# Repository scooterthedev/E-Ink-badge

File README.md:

# Inky - An E-Ink badge

This is an e-ink USB-C PCB badge that I'm building since I loved the Github one so much, and want to make my own! I decided that I wanted to follow a similar design route with the Github Badge so I went with the RP2040 IC.

This was my first time designing an FPC cable from scratch on a PCB! Originally, I wanted to do it to help make a board for my brother, but in the end, I found it too complicated. For this board, I decided to use Gemini to help me, since I wasn't able to find any good documentation of how to properly wire it up.

When I first started this, I though it would take at least 10 hours from when I glanced at the Github Badge, but in the end, it only took me about 4.3 hours which was insanely quick and efficient of my time!

I have attached some photos below outlining the PCB, Schematic and even the 3D rending's on the board!

## Images

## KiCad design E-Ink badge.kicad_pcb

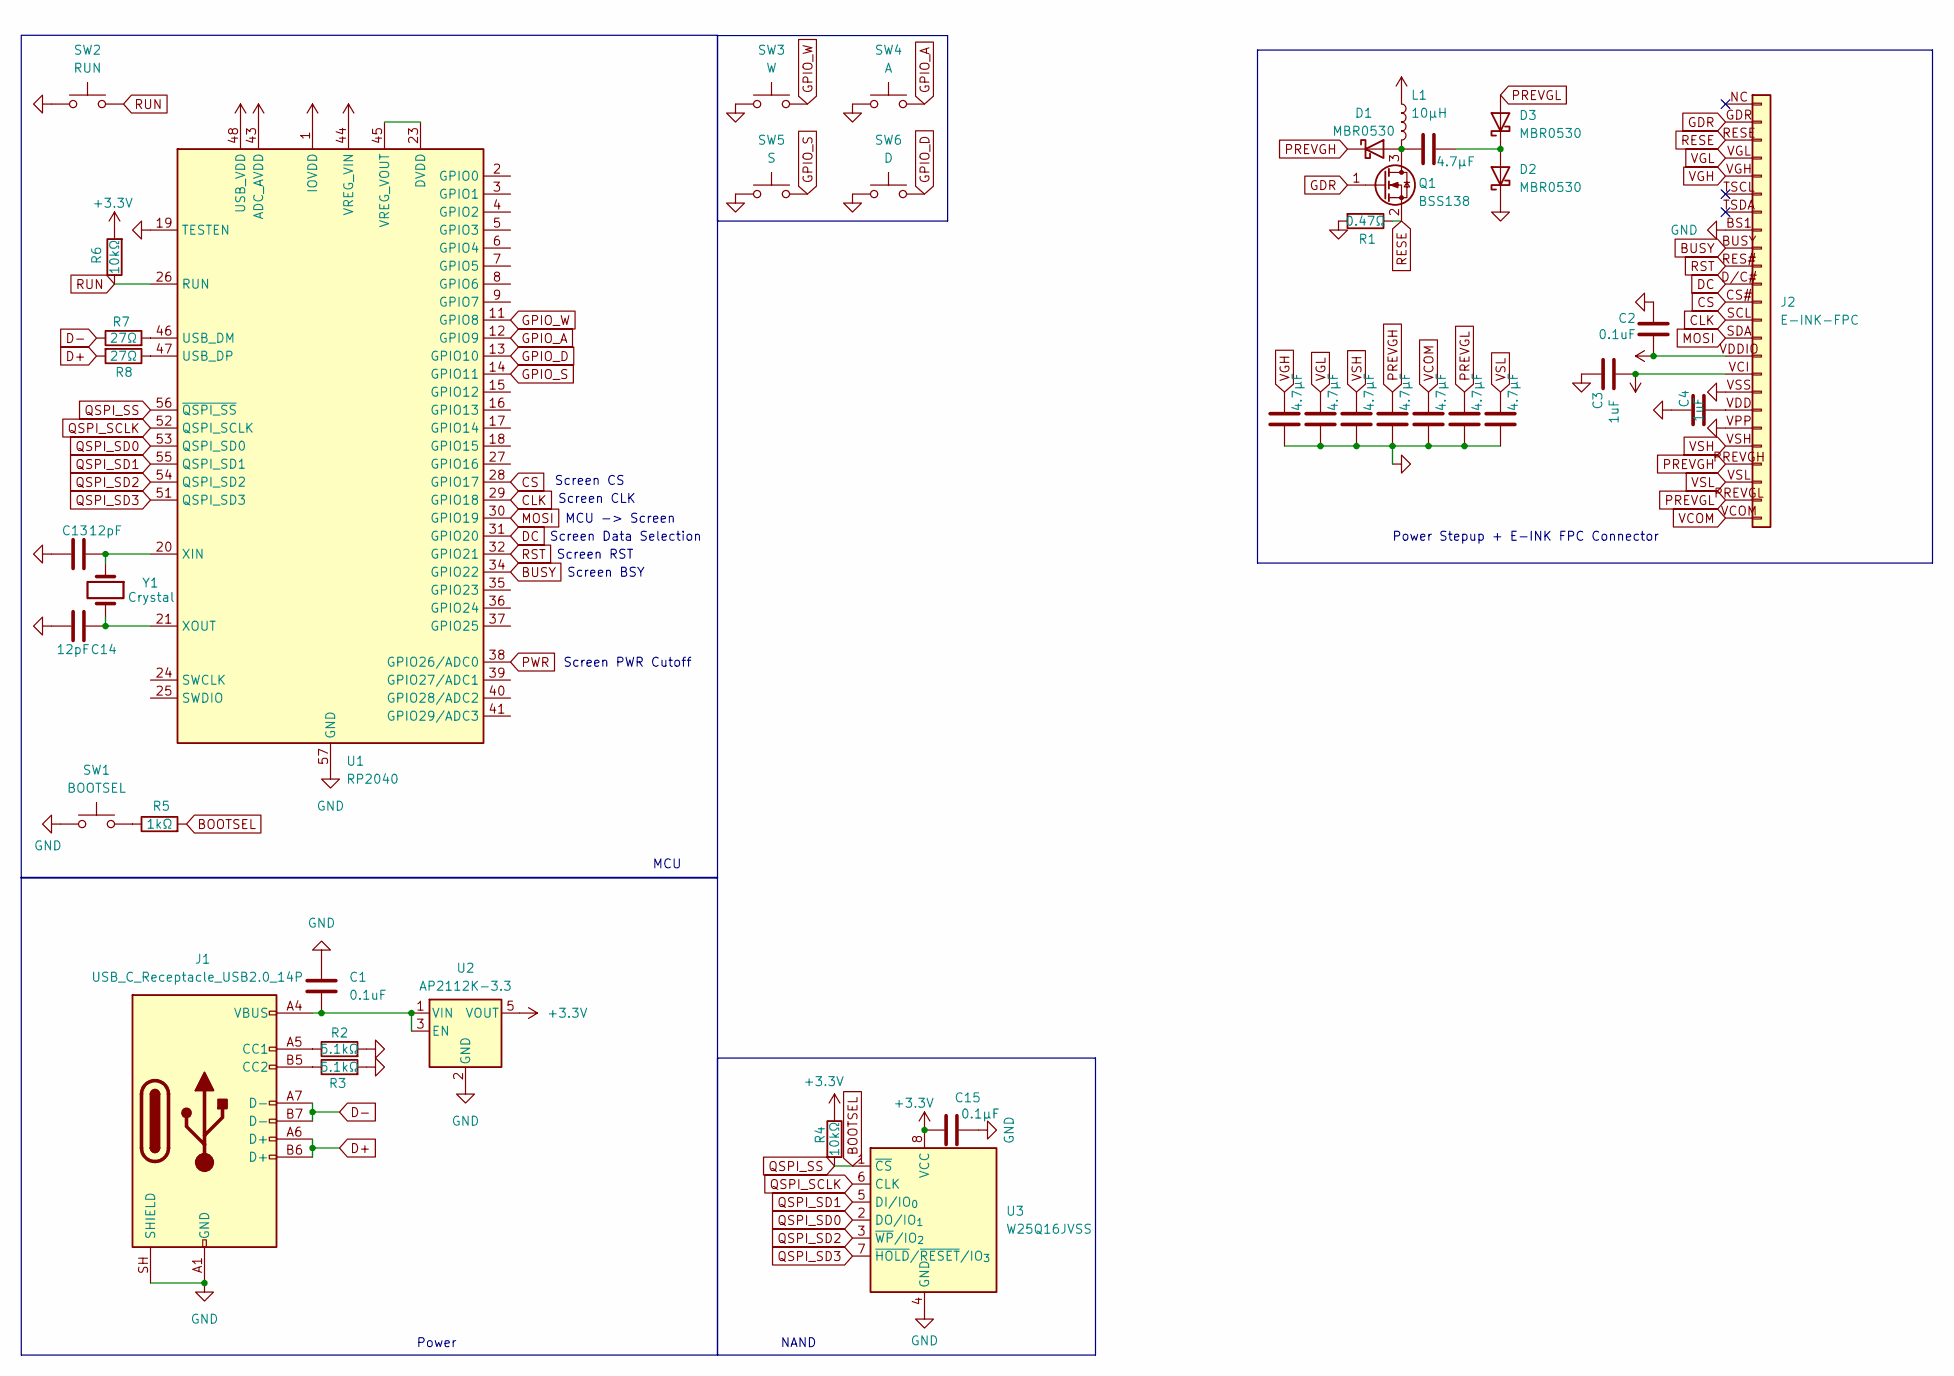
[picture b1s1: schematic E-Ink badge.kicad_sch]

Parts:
C1, C2: 0.1uF; C_0402_1005Metric
C3, C4: 1uF; C_0402_1005Metric
C5, C6, C7, C8, C9, C10, C11, C12: 4.7µF; C_0402_1005Metric
C13, C14: 12pF; C_0402_1005Metric
C15: 0.1µF; C_0402_1005Metric
D1, D2, D3: MBR0530; D_SOD-123
J1: USB_C_Receptacle_USB2.0_14P; USB_C_Receptacle_GCT_USB4105-xx-A_16P_TopMnt_Horizontal
J2: E-INK-FPC; Hirose_FH12-24S-0.5SH_1x24-1MP_P0.50mm_Horizontal
L1: 10µH; L_0805_2012Metric
Q1: BSS138; SOT-23
R1: 0.47Ω; C_0402_1005Metric
R2, R3: 5.1kΩ; C_0402_1005Metric
R4, R6: 10kΩ; C_0402_1005Metric
R5: 1kΩ; C_0402_1005Metric
R7, R8: 27Ω; C_0402_1005Metric
SW1: BOOTSEL; SW_SPST_PTS645Sx43SMTR92
SW2: RUN; SW_SPST_PTS645Sx43SMTR92
SW3: W; SW_SPST_PTS645Sx43SMTR92
SW4: A; SW_SPST_PTS645Sx43SMTR92
SW5: S; SW_SPST_PTS645Sx43SMTR92
SW6: D; SW_SPST_PTS645Sx43SMTR92
U1: RP2040; QFN-56-1EP_7x7mm_P0.4mm_EP3.2x3.2mm
U2: AP2112K-3.3; SOT-23-5
U3: W25Q16JVSS; SOIC-8_5.3x5.3mm_P1.27mm
Y1: Crystal; Crystal_SMD_3215-2Pin_3.2x1.5mm

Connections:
+3.3V: C2.1, C3.1, C15.1, J2.VCI (Pin_16), J2.VDDIO (Pin_15), L1.1, R4.1, R6.2, U1.1 (IOVDD), U1.10 (IOVDD), U1.22 (IOVDD), U1.33 (IOVDD), U1.42 (IOVDD), U1.43 (ADC_AVDD), U1.44 (VREG_VIN), U1.48 (USB_VDD), U1.49 (IOVDD), U2.5 (VOUT), U3.8 (VCC)
BOOTSEL: R4.2, R5.2, U1.56 (~QSPI_SS), U3.1 (~CS)
BUSY: J2.BUSY (Pin_9), U1.34 (GPIO22)
CLK: J2.SCL (Pin_13), U1.29 (GPIO18)
CS: J2.CS# (Pin_12), U1.28 (GPIO17)
D+: J1.A6 (D+), J1.B6 (D+), R8.2
D-: J1.A7 (D-), J1.B7 (D-), R7.1
DC: J2.D/C# (Pin_11), U1.31 (GPIO20)
GDR: J2.GDR (Pin_2), Q1.1 (G)
GND: C1.1, C2.2, C3.2, C4.2, C6.1, C7.1, C8.1, C9.1, C10.1, C11.1, C12.1, C13.2, C14.2, C15.2, D2.1 (K), J1.A1 (GND), J1.A12 (GND), J1.B1 (GND), J1.B12 (GND), J1.SH (SHIELD), J2.BS1 (Pin_8), J2.VPP (Pin_19), J2.VSS (Pin_17), R1.2, R2.2, R3.2, SW1.1, SW2.1, SW3.1, SW4.1, SW5.1, SW6.1, U1.19 (TESTEN), U1.57 (GND), U2.2 (GND), U3.4 (GND)
GPIO_A: SW4.2, U1.12 (GPIO9)
GPIO_D: SW6.2, U1.13 (GPIO10)
GPIO_S: SW5.2, U1.14 (GPIO11)
GPIO_W: SW3.2, U1.11 (GPIO8)
MOSI: J2.SDA (Pin_14), U1.30 (GPIO19)
unnamed: C5.1, D1.2 (A), L1.2, Q1.3 (D)
unnamed: C5.2, D2.2 (A), D3.1 (K)
unnamed: J1.A5 (CC1), R2.1
unnamed: J1.B5 (CC2), R3.1
unnamed: C4.1, J2.VDD (Pin_18)
unnamed: R5.1, SW1.2
unnamed: R7.2, U1.46 (USB_DM)
unnamed: R8.1, U1.47 (USB_DP)
unnamed: U1.23 (DVDD), U1.45 (VREG_VOUT), U1.50 (DVDD)
unnamed: C13.1, U1.20 (XIN), Y1.1
unnamed: C14.1, U1.21 (XOUT), Y1.2
unnamed: C1.2, J1.A4 (VBUS), J1.A9 (VBUS), J1.B4 (VBUS), J1.B9 (VBUS), U2.1 (VIN), U2.3 (EN)
PREVGH: C9.2, D1.1 (K), J2.PREVGH (Pin_21)
PREVGL: C11.2, D3.2 (A), J2.PREVGL (Pin_23)
PWR: U1.38 (GPIO26/ADC0)
QSPI_SCLK: U1.52 (QSPI_SCLK), U3.6 (CLK)
QSPI_SD0: U1.53 (QSPI_SD0), U3.2 (DO/IO_{1})
QSPI_SD1: U1.55 (QSPI_SD1), U3.5 (DI/IO_{0})
QSPI_SD2: U1.54 (QSPI_SD2), U3.3 (~WP/IO_{2})
QSPI_SD3: U1.51 (QSPI_SD3), U3.7 (~HOLD/~RESET/IO_{3})
RESE: J2.RESE (Pin_3), Q1.2 (S), R1.1
RST: J2.RES# (Pin_10), U1.32 (GPIO21)
RUN: R6.1, SW2.2, U1.26 (RUN)
VCOM: C10.2, J2.VCOM (Pin_24)
VGH: C6.2, J2.VGH (Pin_5)
VGL: C7.2, J2.VGL (Pin_4)
VSH: C8.2, J2.VSH (Pin_20)
VSL: C12.2, J2.VSL (Pin_22)

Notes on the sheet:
Screen CS
Screen BSY
Screen PWR Cutoff
Power
Power Stepup + E-INK FPC Connector
MCU
MCU -> Screen
Screen Data Selection
Screen RST
Screen CLK
NAND

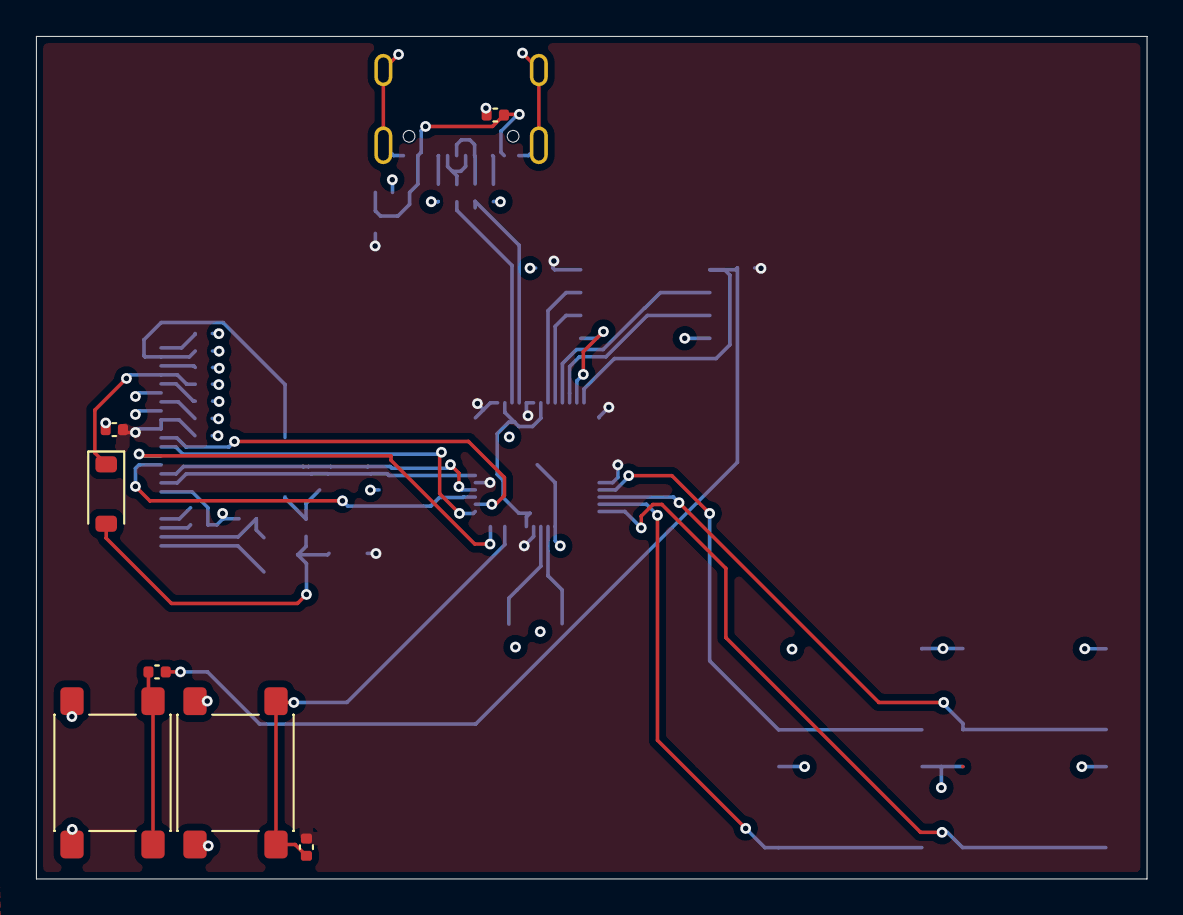
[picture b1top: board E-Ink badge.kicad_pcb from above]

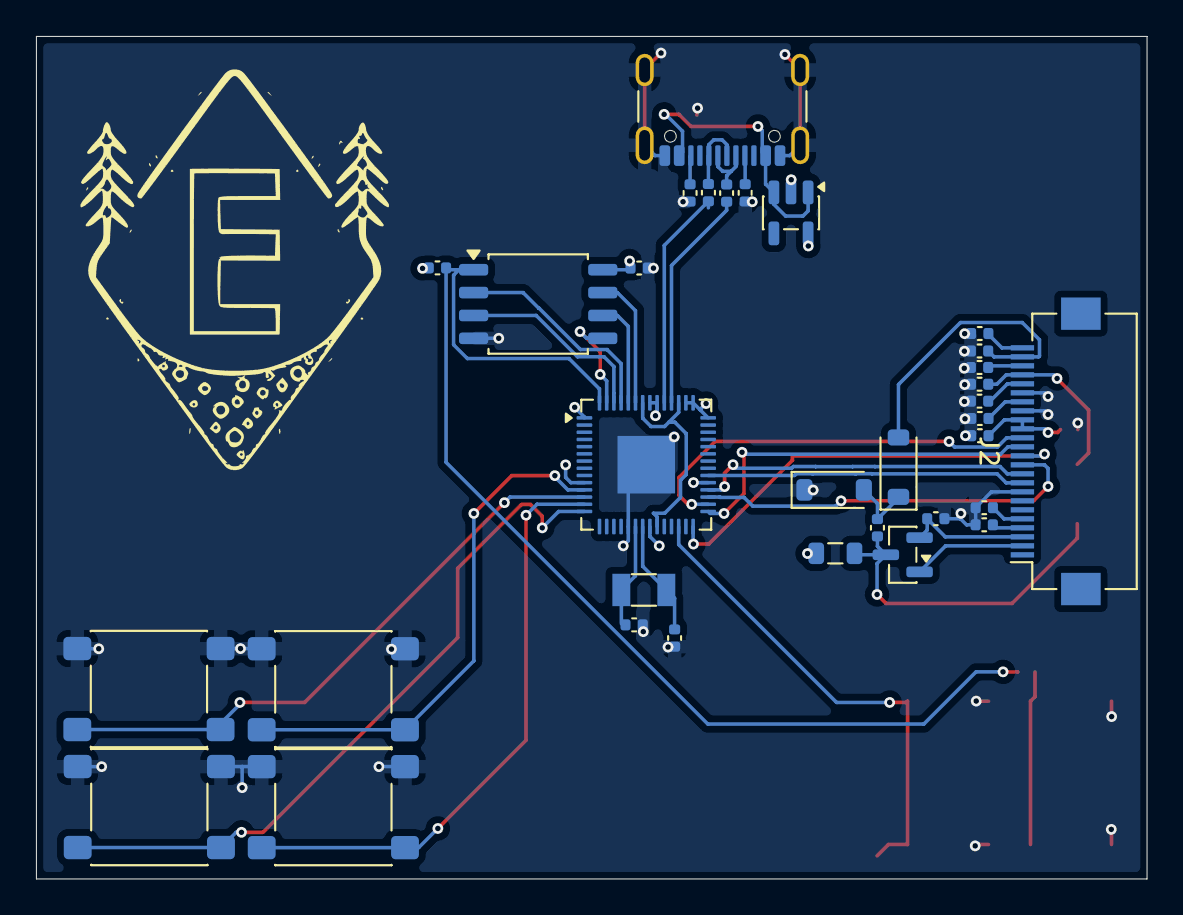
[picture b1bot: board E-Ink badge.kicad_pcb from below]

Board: 2 copper layers, 61.7 x 46.8 mm, 40 parts (33 on the bottom side), 42 nets.

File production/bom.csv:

Designator,Footprint,Quantity,Value,LCSC Part #
"C1, C2",0402,2,0.1uF,
"C10, C11, C12, C5, C6, C7, C8, C9",0402,8,4.7µF,
"C13, C14",0402,2,12pF,
C15,0402,1,0.1µF,
"C3, C4",0402,2,1uF,
"D1, D2, D3",D_SOD-123,3,MBR0530,
J1,USB_C_Receptacle_GCT_USB4105-xx-A_16P_TopMnt_Horizontal,1,USB_C_Receptacle_USB2.0_14P,
J2,Hirose_FH12-24S-0.5SH_1x24-1MP_P0.50mm_Horizontal,1,E-INK-FPC,
L1,0805,1,10µH,
Q1,SOT-23,1,BSS138,
R1,0402,1,0.47Ω,
"R2, R3",0402,2,5.1kΩ,
"R4, R6",0402,2,10kΩ,
R5,0402,1,1kΩ,
"R7, R8",0402,2,27Ω,
SW1,SW_SPST_PTS645Sx43SMTR92,1,BOOTSEL,
SW2,SW_SPST_PTS645Sx43SMTR92,1,RUN,
SW3,SW_SPST_PTS645Sx43SMTR92,1,W,
SW4,SW_SPST_PTS645Sx43SMTR92,1,A,
SW5,SW_SPST_PTS645Sx43SMTR92,1,S,
SW6,SW_SPST_PTS645Sx43SMTR92,1,D,
U1,QFN-56-1EP_7x7mm_P0.4mm_EP3.2x3.2mm,1,RP2040,
U2,SOT-23-5,1,AP2112K-3.3,
U3,SOIC-8_5.3x5.3mm_P1.27mm,1,W25Q16JVSS,
Y1,Crystal_SMD_3215-2Pin_3.2x1.5mm,1,Crystal,

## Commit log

2026-03-06 FPC + NAND Flash done
2026-03-06 BOOTSEL + RUN wired up
2026-03-06 Finished the main schematic besides for some pwr cutoff stuff
2026-03-15 Continued routing the PCB
    routed parts of the MCU, most of the FPC Cable and stuff like that.
2026-03-15 Finally finished routing the whole board!
2026-03-15 added prod files!
2026-03-15 Finished some PCB art + updated prod files
2026-03-15 Update README with project details and images
    Expanded project description and added images.
